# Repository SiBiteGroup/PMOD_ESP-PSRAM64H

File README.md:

# ESP-PSRAM64H

A small PMOD(2x6 pins with 2.54mm pitch) PCB for ESP-PSRAM64H. Also applicable to LY68L6400, APS6404L, etc.

[ESP-PSRAM64 & ESP-PSRAM64H Datasheet](https://cdn-shop.adafruit.com/product-files/4677/4677_esp-psram64_esp-psram64h_datasheet_en.pdf)（[中文](https://www.espressif.com.cn/sites/default/files/documentation/esp-psram64_esp-psram64h_datasheet_cn.pdf)）

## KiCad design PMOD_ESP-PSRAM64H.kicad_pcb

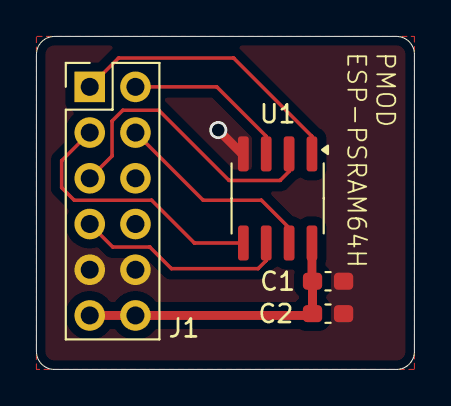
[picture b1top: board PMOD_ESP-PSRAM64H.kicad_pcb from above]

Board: 2 copper layers, 21.0 x 18.5 mm, 4 parts (0 on the bottom side), 8 nets.

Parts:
C1: 100nF; C_0603_1608Metric_Pad1.08x0.95mm_HandSolder
C2: 1uF; C_0603_1608Metric_Pad1.08x0.95mm_HandSolder
J1: Conn_02x06_Odd_Even; PinHeader_2x06_P2.54mm_Vertical
U1: ESP-PSRAM64H; SOIC-8_3.9x4.9mm_P1.27mm

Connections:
/3V3: C1.1, C2.1, J1.11, J1.12, U1.8 (VCC)
/clk: J1.7, U1.6 (SCLK)
/cs_n: J1.1, U1.1 (~CE)
/dp0: J1.3, U1.5 (SI/SIO)
/dp1: J1.5, U1.2 (SO/SIO)
/dp2: J1.2, U1.3 (SIO2)
/dp3: J1.4, U1.7 (SIO3)
GND: C1.2, C2.2, J1.9, J1.10, U1.4 (VSS)

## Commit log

2025-01-13 init
2025-01-13 doc: add README
2025-01-16 pcb: add round corners & update layout
2025-01-16 fix: swap dp0, dp1 pins
2025-01-16 doc: update README
